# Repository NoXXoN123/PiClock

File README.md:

# PiClock
An Original design of an Analog Digital Clock featuring over 210 LEDs and full customization!

# License
Copyright 2025 NoXXoN

All Rights Reserved.

You may view, download, and manufacture physical copies of this PCB and schematic design for **personal, non-commercial use only** (e.g., DIY projects or prototyping).

You may **not**:
- Distribute, share, or sell the design files or derived works.
- Manufacture boards for sale, resale, or commercial deployment.
- Host or mirror this content online.

For commercial licensing, manufacturing rights, or redistribution permissions, please contact:
noxxonyt@gmail.com

This license applies to all files in this project unless explicitly stated otherwise.

# Schematic
 <br>

# PCB and schematic files
PCB: https://github.com/NoXXoN123/PiClock/blob/main/ClockPi.kicad_pcb  
Schematic: https://github.com/NoXXoN123/PiClock/blob/main/ClockPi.kicad_sch  
Kicad_Pro: https://github.com/NoXXoN123/PiClock/blob/main/ClockPi.kicad_pro  
# How to install
Install Thonny, Install MicroPython on a Pi Pico, Save the code below as 'main.py' on the directory of the Raspberry Pi by opening File Manager in Thonny (View > Files) or use Save As and choose the Raspberry Pi.  
# Code:
main.py:

```
import time
from machine import Pin, PWM, ADC

def percent_to_duty(pct):
    return int((pct / 100.0) * 65535)

def get_light_level():
    raw = light_sensor.read_u16()     # 0–65535
    return raw >> 8                   # Scale to 0–255

def set_pwm_all(level):
    pwm_seconds.duty_u16(level)
    pwm_minutes.duty_u16(level)
    pwm_hours.duty_u16(level)

def light_control_loop():
    while True:
        light = get_light_level()

        if light < LIGHT_THRESHOLD:
            set_pwm_all(DIM_LEVEL)
        else:
            set_pwm_all(BRIGHT_LEVEL)

        time.sleep(0.1)  # Check every 100ms
def shift_out(data_pin, clock_pin, latch_pin, data_bytes):
    latch_pin.value(0)
    for byte in data_bytes:
        for bit in range(8):
            data_pin.value((byte >> (7 - bit)) & 1)
            clock_pin.value(1)
            clock_pin.value(0)
    latch_pin.value(1)
def seconds(*bits):
    # bits is a list of 64 bits for 8 chips * 8 bits
    # convert bits to bytes and send
    data_bytes = []
    for i in range(0, 64, 8):
        byte = 0
        for b in bits[i:i+8]:
            byte = (byte << 1) | (b & 1)
        data_bytes.append(byte)
    shift_out(DATA_PIN_SECONDS, CLOCK_PIN_SECONDS, LATCH_PIN_SECONDS, data_bytes)

def minutes(*bits):
    data_bytes = []
    for i in range(0, 64, 8):
        byte = 0
        for b in bits[i:i+8]:
            byte = (byte << 1) | (b & 1)
        data_bytes.append(byte)
    shift_out(DATA_PIN_MINUTES, CLOCK_PIN_MINUTES, LATCH_PIN_MINUTES, data_bytes)

def hours(*bits):
    data_bytes = []
    for i in range(0, 16, 8):
        byte = 0
        for b in bits[i:i+8]:
            byte = (byte << 1) | (b & 1)
        data_bytes.append(byte)
    shift_out(DATA_PIN_HOURS, CLOCK_PIN_HOURS, LATCH_PIN_HOURS, data_bytes)
def seconds(*bits):
    # your code to shift out bits to the seconds chips
    pass

def minutes(*bits):
    # same for minutes
    pass

def hours(*bits):
    # same for hours
    pass

# Pin setup - Don't touch this!
DATA_PIN_SECONDS = Pin(2, Pin.OUT)
CLOCK_PIN_SECONDS = Pin(3, Pin.OUT)
LATCH_PIN_SECONDS = Pin(4, Pin.OUT)

DATA_PIN_MINUTES = Pin(5, Pin.OUT)
CLOCK_PIN_MINUTES = Pin(6, Pin.OUT)
LATCH_PIN_MINUTES = Pin(7, Pin.OUT)

DATA_PIN_HOURS = Pin(9, Pin.OUT)
CLOCK_PIN_HOURS = Pin(8, Pin.OUT)
LATCH_PIN_HOURS = Pin(10, Pin.OUT)

PHOTORESISTOR_PIN = 26 # ADC0
PWM_SECONDS_PIN = 19
PWM_MINUTES_PIN = 20
PWM_HOURS_PIN = 21
BUTTON_HOUR = Pin(17, Pin.IN, Pin.PULL_DOWN)
BUTTON_MINUTE = Pin(16, Pin.IN, Pin.PULL_DOWN)
LED = Pin(25, Pin.OUT)
# Setup Variables - Don't touch this either!
SECOND_CHIPS = 8
MINUTE_CHIPS = 8
HOUR_CHIPS = 2
# USER SETTINGS - Touch this!
PWM_FREQ = 1000 #Hz DEFAULT: 1000
PWM_BRIGHT = percent_to_duty(60)  # DEFAULT: 60
PWM_DIM = percent_to_duty(10)     # DEFAULT: 10
LIGHT_THRESHOLD = 100 # DEFAULT: 100
# ---------------------
light_sensor = ADC(PHOTORESISTOR_PIN)
pwm_seconds = PWM(Pin(PWM_SECONDS_PIN))
pwm_minutes = PWM(Pin(PWM_MINUTES_PIN))
pwm_hours   = PWM(Pin(PWM_HOURS_PIN))
for pwm in (pwm_seconds, pwm_minutes, pwm_hours):
    pwm.freq(PWM_FREQ)

seconds_buffer = bytearray(SECOND_CHIPS)
minutes_buffer = bytearray(MINUTE_CHIPS)
hours_buffer = bytearray(HOUR_CHIPS)

# ---------------- Functions ----------------
def boot_animation_chase():
    for i in range(64):  # 64 steps for seconds and minutes
        sec_pattern = [0 if j == i else 1 for j in range(64)]
        min_pattern = [0 if j == (i + 20) % 64 else 1 for j in range(64)]  # offset for visual effect
        hr_pattern  = [0 if j == (i % 16) else 1 for j in range(16)]       # wrap 0–15

        seconds(*sec_pattern)
        minutes(*min_pattern)
        hours(*hr_pattern)

        time.sleep(0.03)

def fast_forward_boot(cycle_duration_sec=10):
    total_seconds = 12 * 60 * 60  # 12 hours = 43200 seconds
    delay = cycle_duration_sec / total_seconds

    for seconds_passed in range(total_seconds):
        sec = seconds_passed % 60
        min = (seconds_passed // 60) % 60
        hr  = (seconds_passed // 3600) % 12  # 12-hour format

        sec_buf = [1] * 64
        sec_buf[sec] = 0  # active low
        seconds(*sec_buf)

        min_buf = [1] * 64
        min_buf[min] = 0
        minutes(*min_buf)

        hr_buf = [1] * 16
        hr_buf[hr] = 0
        hours(*hr_buf)

        time.sleep(delay)

def run_clock():
    last_sec_update = 0
    last_min_update = 0
    last_hour_update = 0

    sec = 0
    minute = 0
    hour = 0

    last_button_hour = 0
    last_button_minute = 0
    debounce_ms = 200  # debounce delay

    led_on_time = 0
    led_duration = 200  # ms to keep LED on visibly

    while True:
        now = time.ticks_ms()

        if BUTTON_HOUR.value() == 1 and time.ticks_diff(now, last_button_hour) > debounce_ms:
            hour = (hour + 1) % 12
            hours(*[0 if i == hour else 1 for i in range(16)])
            last_button_hour = now
            last_hour_update = now

        if BUTTON_MINUTE.value() == 1 and time.ticks_diff(now, last_button_minute) > debounce_ms:
            minute = (minute + 1) % 60
            minutes(*[0 if i == minute else 1 for i in range(64)])
            last_button_minute = now
            last_min_update = now

        if time.ticks_diff(now, last_sec_update) >= 1000:
            sec = (sec + 1) % 60
            seconds(*[0 if i == sec else 1 for i in range(64)])
            last_sec_update = now

            LED.value(1)
            led_on_time = now

        if LED.value() == 1 and time.ticks_diff(now, led_on_time) > led_duration:
            LED.value(0)

        if time.ticks_diff(now, last_min_update) >= 60000:
            minute = (minute + 1) % 60
            minutes(*[0 if i == minute else 1 for i in range(64)])
            last_min_update = now

        if time.ticks_diff(now, last_hour_update) >= 3600000:
            hour = (hour + 1) % 12
            hours(*[0 if i == hour else 1 for i in range(16)])
            last_hour_update = now

        light = get_light_level()
        if light < LIGHT_THRESHOLD:
            set_pwm_all(PWM_DIM)
        else:
            set_pwm_all(PWM_BRIGHT)

        time.sleep(0.01) 

boot_animation_chase()
fast_forward_boot(10) # <-- 10 Seconds
run_clock()
```

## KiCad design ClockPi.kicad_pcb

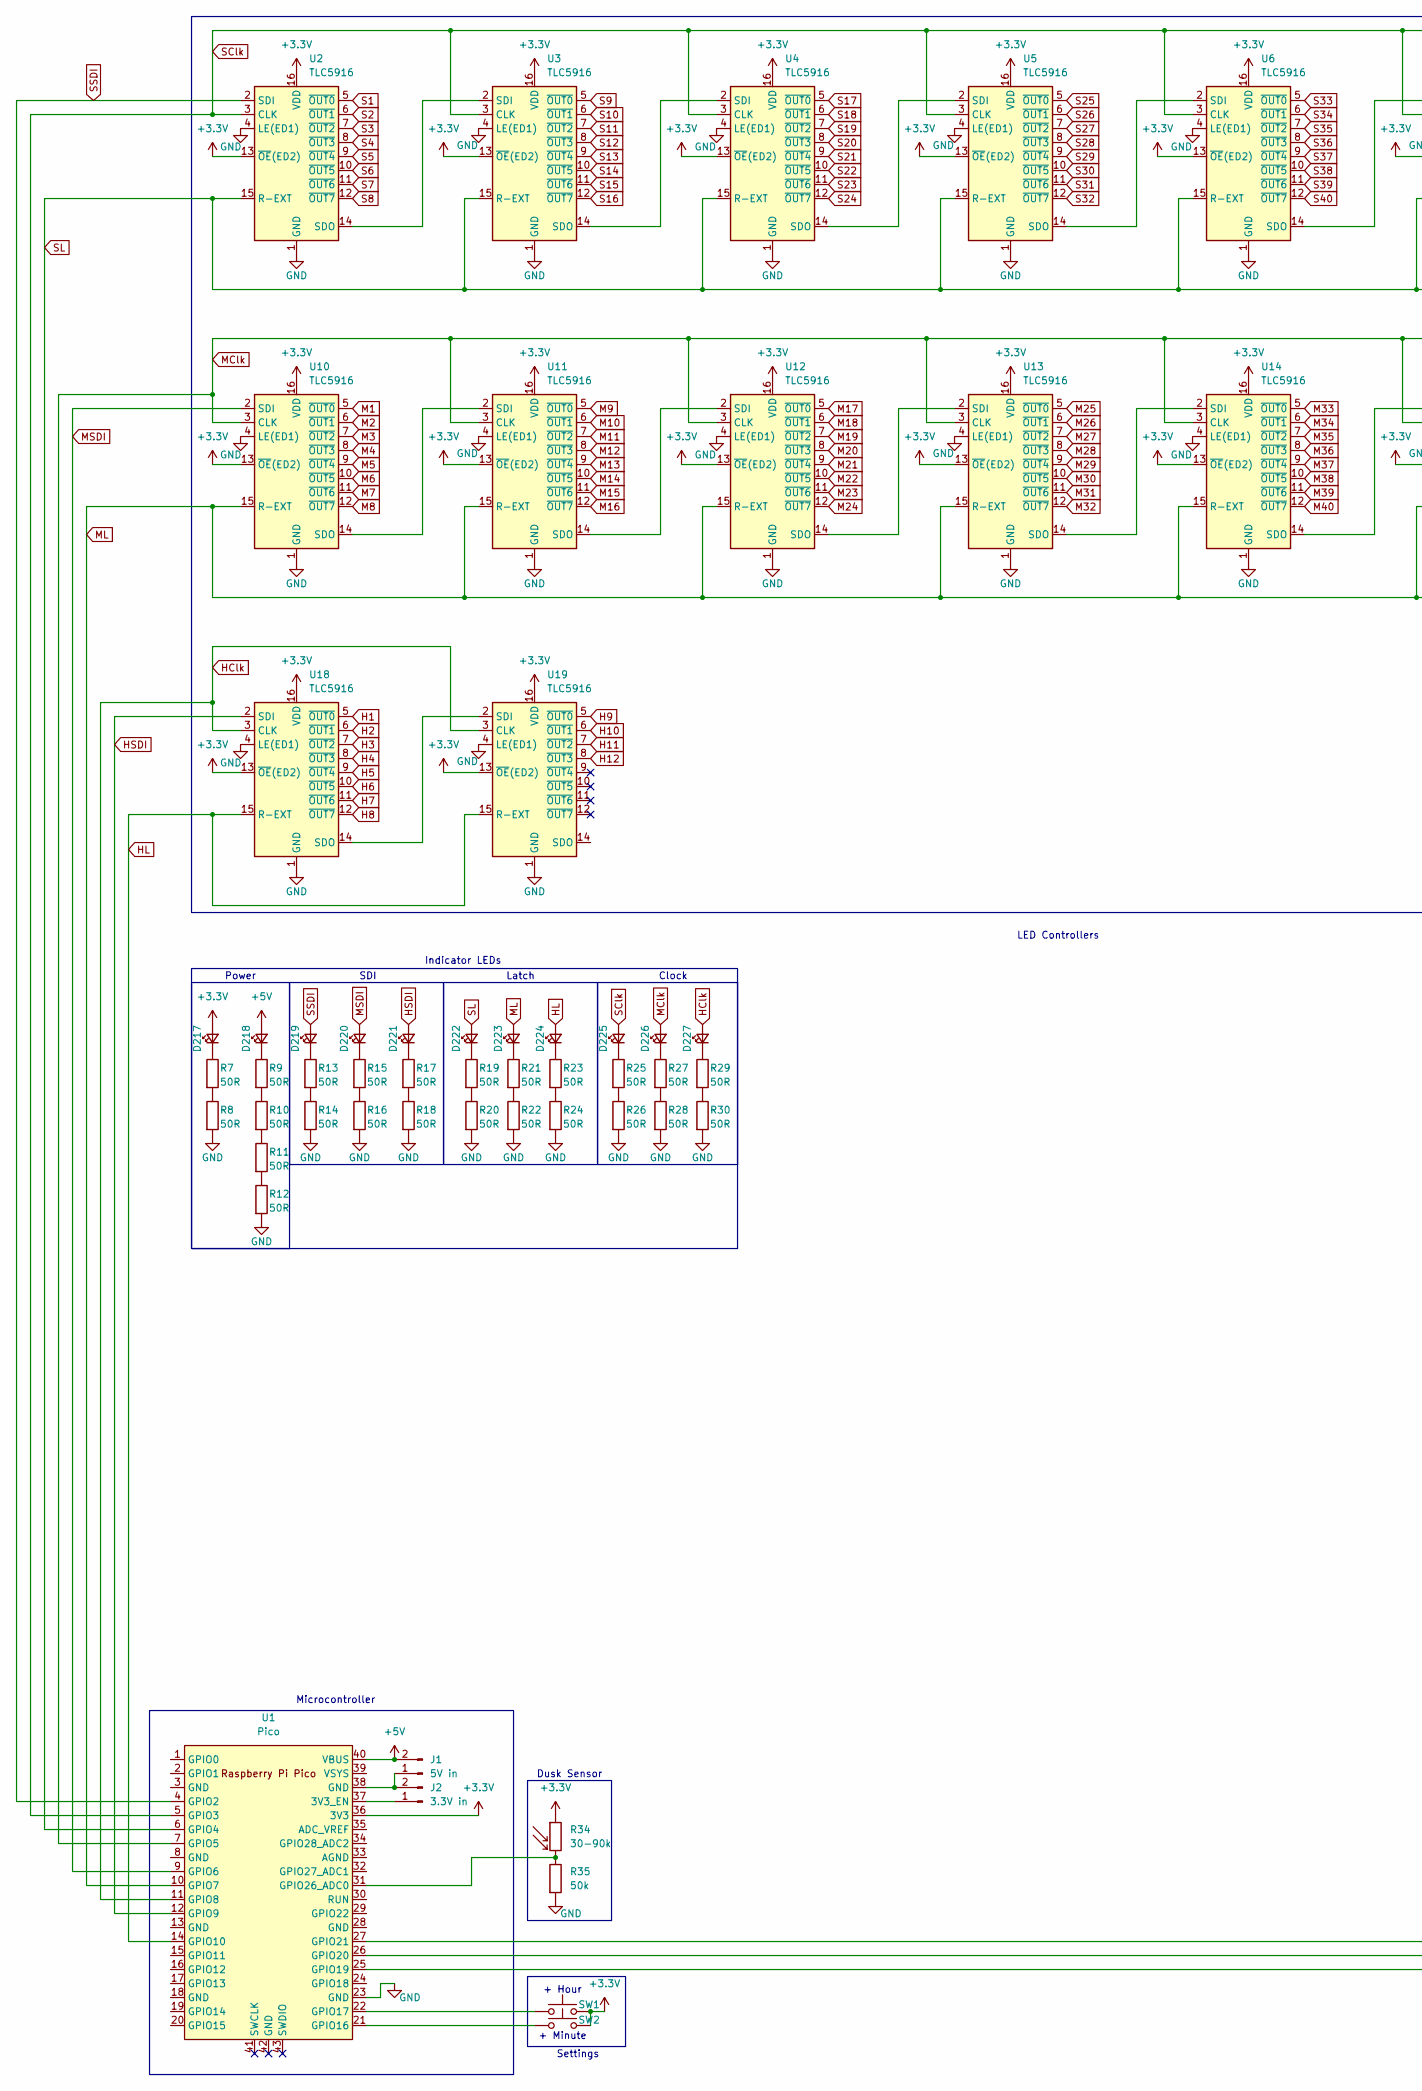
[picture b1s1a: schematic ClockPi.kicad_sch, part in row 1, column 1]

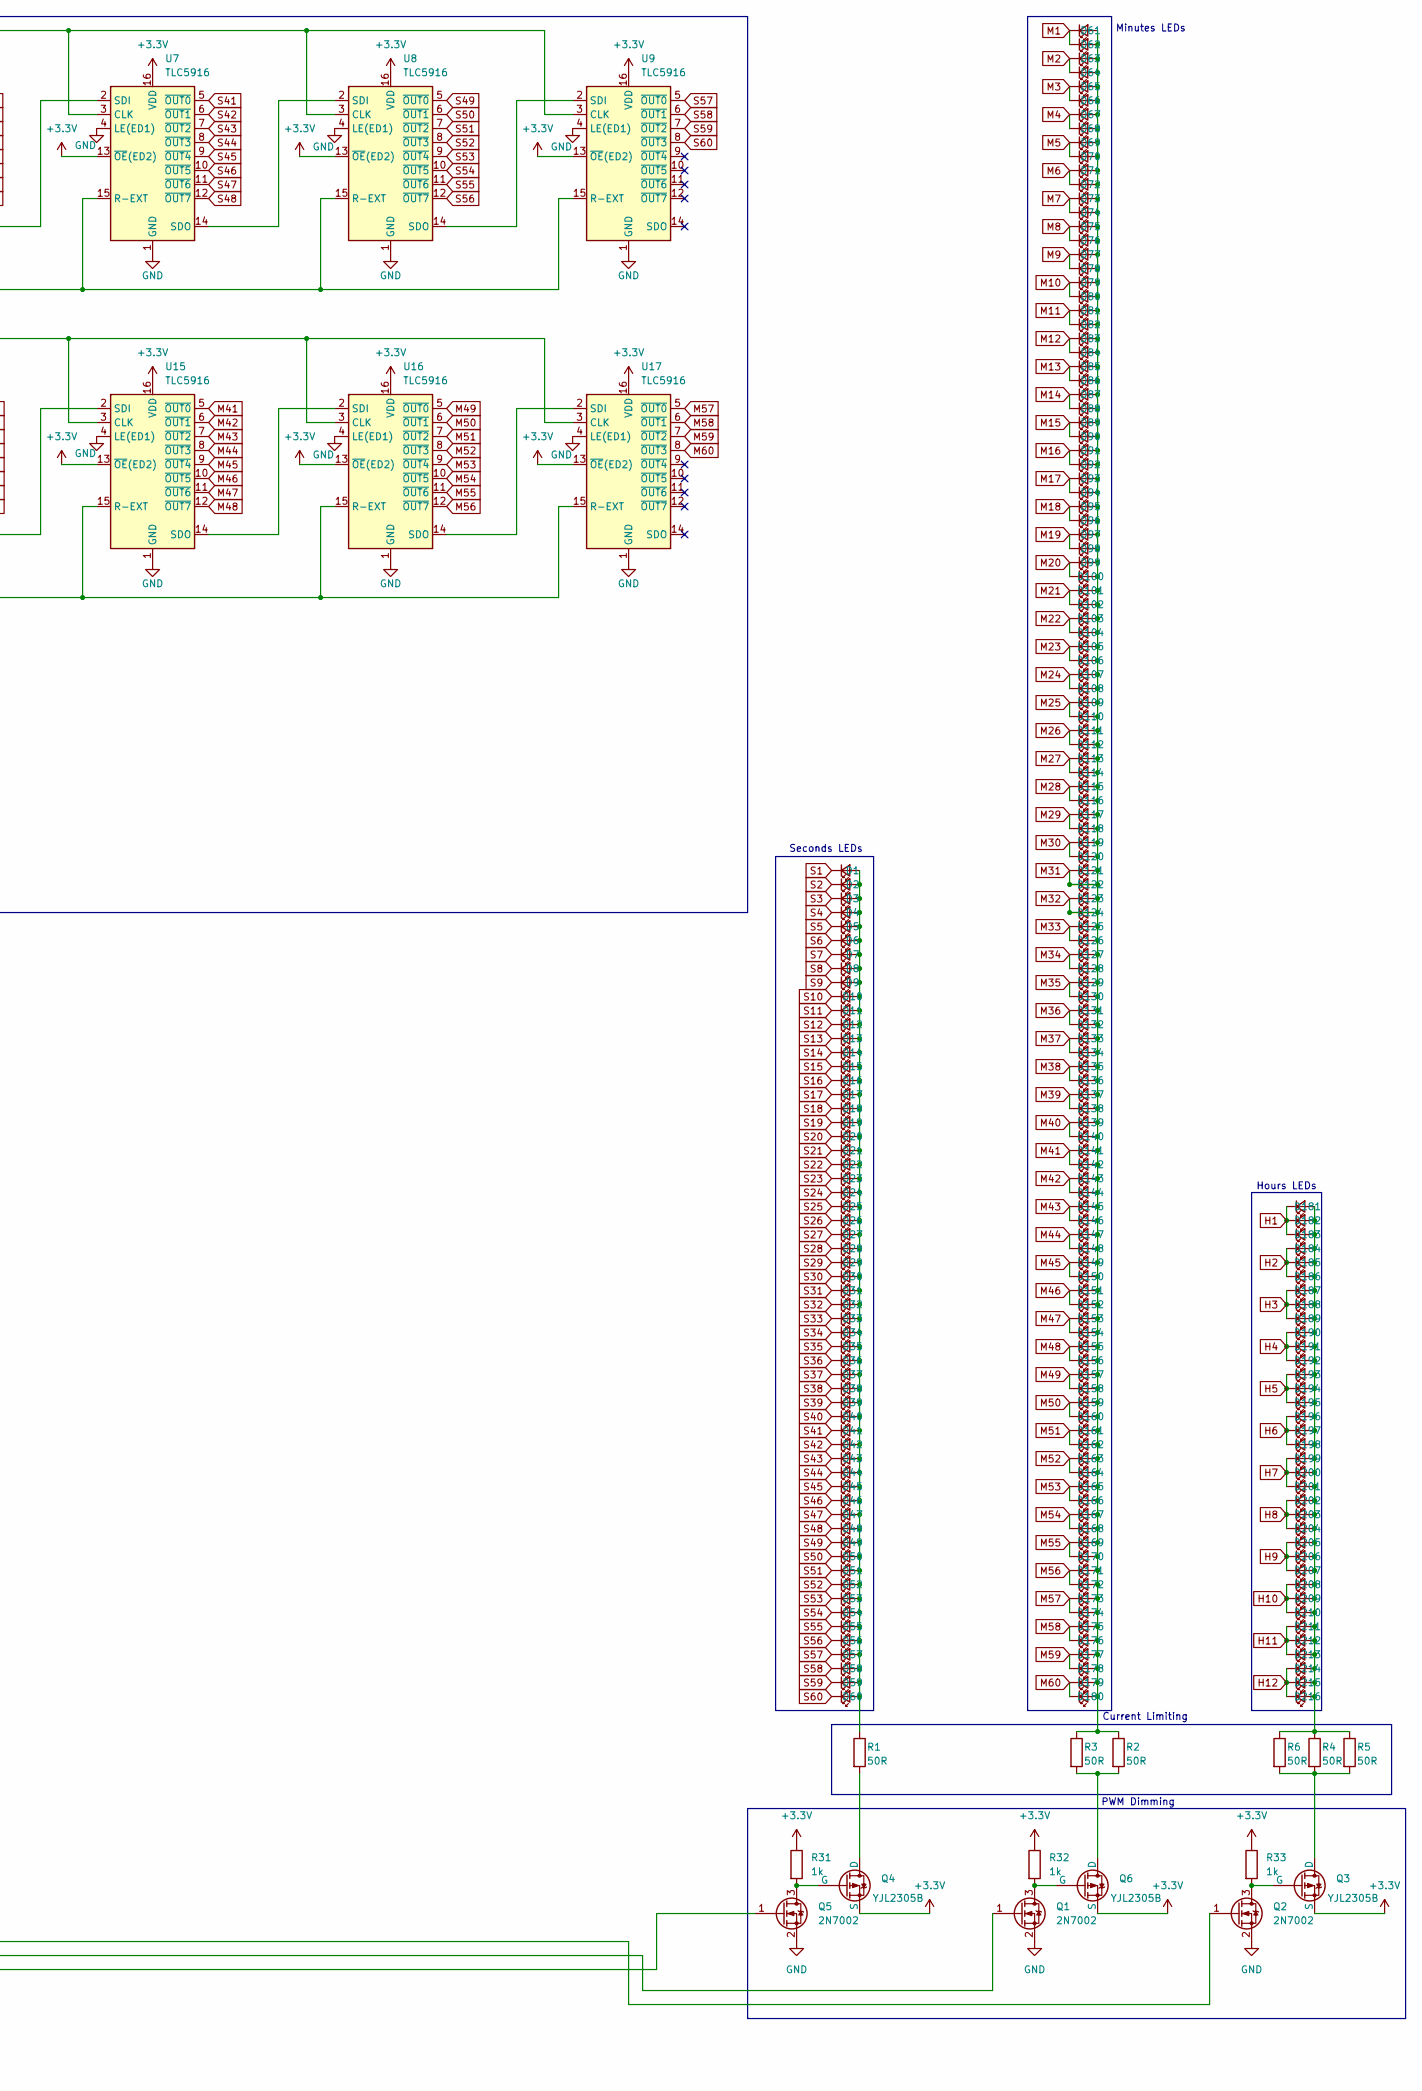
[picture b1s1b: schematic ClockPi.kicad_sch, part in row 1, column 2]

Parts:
D1, D2, D3, D4, D5, D6, D7, D8, D9, D10, D11, D12, D13, D14, D15, D16, D17, D18, D19, D20, D21, D22, D23, D24, D25, D26, D27, D28, D29, D30, D31, D32, D33, D34, D35, D36, D37, D38, D39, D40, D41, D42, D43, D44, D45, D46, D47, D48, D49, D50, D51, D52, D53, D54, D55, D56, D57, D58, D59, D60, D61, D62, D63, D64, D65, D66, D67, D68, D69, D70, D71, D72, D73, D74, D75, D76, D77, D78, D79, D80, D81, D82, D83, D84, D85, D86, D87, D88, D89, D90, D91, D92, D93, D94, D95, D96, D97, D98, D99, D100, D101, D102, D103, D104, D105, D106, D107, D108, D109, D110, D111, D112, D113, D114, D115, D116, D117, D118, D119, D120, D121, D122, D123, D124, D125, D126, D127, D128, D129, D130, D131, D132, D133, D134, D135, D136, D137, D138, D139, D140, D141, D142, D143, D144, D145, D146, D147, D148, D149, D150, D151, D152, D153, D154, D155, D156, D157, D158, D159, D160, D161, D162, D163, D164, D165, D166, D167, D168, D169, D170, D171, D172, D173, D174, D175, D176, D177, D178, D179, D180, D181, D182, D183, D184, D185, D186, D187, D188, D189, D190, D191, D192, D193, D194, D195, D196, D197, D198, D199, D200, D201, D202, D203, D204, D205, D206, D207, D208, D209, D210, D211, D212, D213, D214, D215, D216, D217, D218, D219, D220, D221, D222, D223, D224, D225, D226, D227: LED_Small; LED_0805_2012Metric_Pad1.15x1.40mm_HandSolder
J1: 5V in; PinHeader_1x02_P2.54mm_Vertical
J2: 3.3V in; PinHeader_1x02_P2.54mm_Vertical
Q1, Q2, Q5: 2N7002; SOT-23
Q3, Q4, Q6: YJL2305B; SOT-323_SC-70_Handsoldering
R1, R2, R3, R4, R5, R6, R7, R8, R9, R10, R11, R12, R13, R14, R15, R16, R17, R18, R19, R20, R21, R22, R23, R24, R25, R26, R27, R28, R29, R30: 50R; R_0402_1005Metric_Pad0.72x0.64mm_HandSolder
R31, R32, R33: 1k; R_0402_1005Metric_Pad0.72x0.64mm_HandSolder
R34: 30-90k; R_LDR_5.1x4.3mm_P3.4mm_Vertical
R35: 50k; R_0402_1005Metric_Pad0.72x0.64mm_HandSolder
SW1, SW2: SW_Push; SW_DIP_SPSTx01_Slide_6.7x4.1mm_W6.73mm_P2.54mm_LowProfile_J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
U1: Pico; RaspberryPi_Pico_SMD_HandSolder
U2, U3, U4, U5, U6, U7, U8, U9, U10, U11, U12, U13, U14, U15, U16, U17, U18, U19: TLC5916; SO-16_3.9x9.9mm_P1.27mm

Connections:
+3.3V: D217.2 (A), Q3.3 (S), Q4.3 (S), Q6.3 (S), R31.1, R32.1, R33.1, R34.1, SW1.2, SW2.2, U1.36 (3V3), U2.13 (~OE(ED2)), U2.16 (VDD), U3.13 (~OE(ED2)), U3.16 (VDD), U4.13 (~OE(ED2)), U4.16 (VDD), U5.13 (~OE(ED2)), U5.16 (VDD), U6.13 (~OE(ED2)), U6.16 (VDD), U7.13 (~OE(ED2)), U7.16 (VDD), U8.13 (~OE(ED2)), U8.16 (VDD), U9.13 (~OE(ED2)), U9.16 (VDD), U10.13 (~OE(ED2)), U10.16 (VDD), U11.13 (~OE(ED2)), U11.16 (VDD), U12.13 (~OE(ED2)), U12.16 (VDD), U13.13 (~OE(ED2)), U13.16 (VDD), U14.13 (~OE(ED2)), U14.16 (VDD), U15.13 (~OE(ED2)), U15.16 (VDD), U16.13 (~OE(ED2)), U16.16 (VDD), U17.13 (~OE(ED2)), U17.16 (VDD), U18.13 (~OE(ED2)), U18.16 (VDD), U19.13 (~OE(ED2)), U19.16 (VDD)
+5V: D218.2 (A), J1.2, U1.40 (VBUS)
GND: Q1.2 (S), Q2.2 (S), Q5.2 (S), R8.2, R12.2, R14.2, R16.2, R18.2, R20.2, R22.2, R24.2, R26.2, R28.2, R30.2, R35.2, U1.23 (GND), U2.1 (GND), U2.4 (LE(ED1)), U3.1 (GND), U3.4 (LE(ED1)), U4.1 (GND), U4.4 (LE(ED1)), U5.1 (GND), U5.4 (LE(ED1)), U6.1 (GND), U6.4 (LE(ED1)), U7.1 (GND), U7.4 (LE(ED1)), U8.1 (GND), U8.4 (LE(ED1)), U9.1 (GND), U9.4 (LE(ED1)), U10.1 (GND), U10.4 (LE(ED1)), U11.1 (GND), U11.4 (LE(ED1)), U12.1 (GND), U12.4 (LE(ED1)), U13.1 (GND), U13.4 (LE(ED1)), U14.1 (GND), U14.4 (LE(ED1)), U15.1 (GND), U15.4 (LE(ED1)), U16.1 (GND), U16.4 (LE(ED1)), U17.1 (GND), U17.4 (LE(ED1)), U18.1 (GND), U18.4 (LE(ED1)), U19.1 (GND), U19.4 (LE(ED1))
H1: D181.1 (K), D182.1 (K), D183.1 (K), U18.5 (~OUT0)
H2: D184.1 (K), D185.1 (K), D186.1 (K), U18.6 (~OUT1)
H3: D187.1 (K), D188.1 (K), D189.1 (K), U18.7 (~OUT2)
H4: D190.1 (K), D191.1 (K), D192.1 (K), U18.8 (~OUT3)
H5: D193.1 (K), D194.1 (K), D195.1 (K), U18.9 (~OUT4)
H6: D196.1 (K), D197.1 (K), D198.1 (K), U18.10 (~OUT5)
H7: D199.1 (K), D200.1 (K), D201.1 (K), U18.11 (~OUT6)
H8: D202.1 (K), D203.1 (K), D204.1 (K), U18.12 (~OUT7)
H9: D205.1 (K), D206.1 (K), D207.1 (K), U19.5 (~OUT0)
H10: D208.1 (K), D209.1 (K), D210.1 (K), U19.6 (~OUT1)
H11: D211.1 (K), D212.1 (K), D213.1 (K), U19.7 (~OUT2)
H12: D214.1 (K), D215.1 (K), D216.1 (K), U19.8 (~OUT3)
HClk: D227.2 (A), U1.11 (GPIO8), U18.3 (CLK), U19.3 (CLK)
HL: D224.2 (A), U1.14 (GPIO10), U18.15 (R-EXT), U19.15 (R-EXT)
HSDI: D221.2 (A), U1.12 (GPIO9), U18.2 (SDI)
M1: D61.1 (K), D62.1 (K), U10.5 (~OUT0)
M2: D63.1 (K), D64.1 (K), U10.6 (~OUT1)
M3: D65.1 (K), D66.1 (K), U10.7 (~OUT2)
M4: D67.1 (K), D68.1 (K), U10.8 (~OUT3)
M5: D69.1 (K), D70.1 (K), U10.9 (~OUT4)
M6: D71.1 (K), D72.1 (K), U10.10 (~OUT5)
M7: D73.1 (K), D74.1 (K), U10.11 (~OUT6)
M8: D75.1 (K), D76.1 (K), U10.12 (~OUT7)
M9: D77.1 (K), D78.1 (K), U11.5 (~OUT0)
M10: D79.1 (K), D80.1 (K), U11.6 (~OUT1)
M11: D81.1 (K), D82.1 (K), U11.7 (~OUT2)
M12: D83.1 (K), D84.1 (K), U11.8 (~OUT3)
M13: D85.1 (K), D86.1 (K), U11.9 (~OUT4)
M14: D87.1 (K), D88.1 (K), U11.10 (~OUT5)
M15: D89.1 (K), D90.1 (K), U11.11 (~OUT6)
M16: D91.1 (K), D92.1 (K), U11.12 (~OUT7)
M17: D93.1 (K), D94.1 (K), U12.5 (~OUT0)
M18: D95.1 (K), D96.1 (K), U12.6 (~OUT1)
M19: D97.1 (K), D98.1 (K), U12.7 (~OUT2)
M20: D99.1 (K), D100.1 (K), U12.8 (~OUT3)
M21: D101.1 (K), D102.1 (K), U12.9 (~OUT4)
M22: D103.1 (K), D104.1 (K), U12.10 (~OUT5)
M23: D105.1 (K), D106.1 (K), U12.11 (~OUT6)
M24: D107.1 (K), D108.1 (K), U12.12 (~OUT7)
M25: D109.1 (K), D110.1 (K), U13.5 (~OUT0)
M26: D111.1 (K), D112.1 (K), U13.6 (~OUT1)
M27: D113.1 (K), D114.1 (K), U13.7 (~OUT2)
M28: D115.1 (K), D116.1 (K), U13.8 (~OUT3)
M29: D117.1 (K), D118.1 (K), U13.9 (~OUT4)
M30: D119.1 (K), D120.1 (K), U13.10 (~OUT5)
M31: D61.2 (A), D62.2 (A), D63.2 (A), D64.2 (A), D65.2 (A), D66.2 (A), D67.2 (A), D68.2 (A), D69.2 (A), D70.2 (A), D71.2 (A), D72.2 (A), D73.2 (A), D74.2 (A), D75.2 (A), D76.2 (A), D77.2 (A), D78.2 (A), D79.2 (A), D80.2 (A), D81.2 (A), D82.2 (A), D83.2 (A), D84.2 (A), D85.2 (A), D86.2 (A), D87.2 (A), D88.2 (A), D89.2 (A), D90.2 (A), D91.2 (A), D92.2 (A), D93.2 (A), D94.2 (A), D95.2 (A), D96.2 (A), D97.2 (A), D98.2 (A), D99.2 (A), D100.2 (A), D101.2 (A), D102.2 (A), D103.2 (A), D104.2 (A), D105.2 (A), D106.2 (A), D107.2 (A), D108.2 (A), D109.2 (A), D110.2 (A), D111.2 (A), D112.2 (A), D113.2 (A), D114.2 (A), D115.2 (A), D116.2 (A), D117.2 (A), D118.2 (A), D119.2 (A), D120.2 (A), D121.1 (K), D121.2 (A), D122.1 (K), D122.2 (A), D123.1 (K), D123.2 (A), D124.1 (K), D124.2 (A), D125.2 (A), D126.2 (A), D127.2 (A), D128.2 (A), D129.2 (A), D130.2 (A), D131.2 (A), D132.2 (A), D133.2 (A), D134.2 (A), D135.2 (A), D136.2 (A), D137.2 (A), D138.2 (A), D139.2 (A), D140.2 (A), D141.2 (A), D142.2 (A), D143.2 (A), D144.2 (A), D145.2 (A), D146.2 (A), D147.2 (A), D148.2 (A), D149.2 (A), D150.2 (A), D151.2 (A), D152.2 (A), D153.2 (A), D154.2 (A), D155.2 (A), D156.2 (A), D157.2 (A), D158.2 (A), D159.2 (A), D160.2 (A), D161.2 (A), D162.2 (A), D163.2 (A), D164.2 (A), D165.2 (A), D166.2 (A), D167.2 (A), D168.2 (A), D169.2 (A), D170.2 (A), D171.2 (A), D172.2 (A), D173.2 (A), D174.2 (A), D175.2 (A), D176.2 (A), D177.2 (A), D178.2 (A), D179.2 (A), D180.2 (A), R2.1, R3.1, U13.11 (~OUT6), U13.12 (~OUT7)
M33: D125.1 (K), D126.1 (K), U14.5 (~OUT0)
M34: D127.1 (K), D128.1 (K), U14.6 (~OUT1)
M35: D129.1 (K), D130.1 (K), U14.7 (~OUT2)
M36: D131.1 (K), D132.1 (K), U14.8 (~OUT3)
M37: D133.1 (K), D134.1 (K), U14.9 (~OUT4)
M38: D135.1 (K), D136.1 (K), U14.10 (~OUT5)
M39: D137.1 (K), D138.1 (K), U14.11 (~OUT6)
M40: D139.1 (K), D140.1 (K), U14.12 (~OUT7)
M41: D141.1 (K), D142.1 (K), U15.5 (~OUT0)
M42: D143.1 (K), D144.1 (K), U15.6 (~OUT1)
M43: D145.1 (K), D146.1 (K), U15.7 (~OUT2)
M44: D147.1 (K), D148.1 (K), U15.8 (~OUT3)
M45: D149.1 (K), D150.1 (K), U15.9 (~OUT4)
M46: D151.1 (K), D152.1 (K), U15.10 (~OUT5)
M47: D153.1 (K), D154.1 (K), U15.11 (~OUT6)
M48: D155.1 (K), D156.1 (K), U15.12 (~OUT7)
M49: D157.1 (K), D158.1 (K), U16.5 (~OUT0)
M50: D159.1 (K), D160.1 (K), U16.6 (~OUT1)
M51: D161.1 (K), D162.1 (K), U16.7 (~OUT2)
M52: D163.1 (K), D164.1 (K), U16.8 (~OUT3)
M53: D165.1 (K), D166.1 (K), U16.9 (~OUT4)
M54: D167.1 (K), D168.1 (K), U16.10 (~OUT5)
M55: D169.1 (K), D170.1 (K), U16.11 (~OUT6)
M56: D171.1 (K), D172.1 (K), U16.12 (~OUT7)
M57: D173.1 (K), D174.1 (K), U17.5 (~OUT0)
M58: D175.1 (K), D176.1 (K), U17.6 (~OUT1)
M59: D177.1 (K), D178.1 (K), U17.7 (~OUT2)
M60: D179.1 (K), D180.1 (K), U17.8 (~OUT3)
MClk: D226.2 (A), U1.7 (GPIO5), U10.3 (CLK), U11.3 (CLK), U12.3 (CLK), U13.3 (CLK), U14.3 (CLK), U15.3 (CLK), U16.3 (CLK), U17.3 (CLK)
ML: D223.2 (A), U1.10 (GPIO7), U10.15 (R-EXT), U11.15 (R-EXT), U12.15 (R-EXT), U13.15 (R-EXT), U14.15 (R-EXT), U15.15 (R-EXT), U16.15 (R-EXT), U17.15 (R-EXT)
MSDI: D220.2 (A), U1.9 (GPIO6), U10.2 (SDI)
unnamed: D1.2 (A), D2.2 (A), D3.2 (A), D4.2 (A), D5.2 (A), D6.2 (A), D7.2 (A), D8.2 (A), D9.2 (A), D10.2 (A), D11.2 (A), D12.2 (A), D13.2 (A), D14.2 (A), D15.2 (A), D16.2 (A), D17.2 (A), D18.2 (A), D19.2 (A), D20.2 (A), D21.2 (A), D22.2 (A), D23.2 (A), D24.2 (A), D25.2 (A), D26.2 (A), D27.2 (A), D28.2 (A), D29.2 (A), D30.2 (A), D31.2 (A), D32.2 (A), D33.2 (A), D34.2 (A), D35.2 (A), D36.2 (A), D37.2 (A), D38.2 (A), D39.2 (A), D40.2 (A), D41.2 (A), D42.2 (A), D43.2 (A), D44.2 (A), D45.2 (A), D46.2 (A), D47.2 (A), D48.2 (A), D49.2 (A), D50.2 (A), D51.2 (A), D52.2 (A), D53.2 (A), D54.2 (A), D55.2 (A), D56.2 (A), D57.2 (A), D58.2 (A), D59.2 (A), D60.2 (A), R1.1
unnamed: D181.2 (A), D182.2 (A), D183.2 (A), D184.2 (A), D185.2 (A), D186.2 (A), D187.2 (A), D188.2 (A), D189.2 (A), D190.2 (A), D191.2 (A), D192.2 (A), D193.2 (A), D194.2 (A), D195.2 (A), D196.2 (A), D197.2 (A), D198.2 (A), D199.2 (A), D200.2 (A), D201.2 (A), D202.2 (A), D203.2 (A), D204.2 (A), D205.2 (A), D206.2 (A), D207.2 (A), D208.2 (A), D209.2 (A), D210.2 (A), D211.2 (A), D212.2 (A), D213.2 (A), D214.2 (A), D215.2 (A), D216.2 (A), R4.1, R5.1, R6.1
unnamed: D217.1 (K), R7.1
unnamed: D218.1 (K), R9.1
unnamed: D219.1 (K), R13.1
unnamed: D220.1 (K), R15.1
unnamed: D221.1 (K), R17.1
unnamed: D222.1 (K), R19.1
unnamed: D223.1 (K), R21.1
unnamed: D224.1 (K), R23.1
unnamed: D225.1 (K), R25.1
unnamed: D226.1 (K), R27.1
unnamed: D227.1 (K), R29.1
unnamed: J1.1, J2.2, U1.38 (GND)
unnamed: J2.1, U1.37 (3V3_EN)
unnamed: Q1.3 (D), Q6.2 (G), R32.2
unnamed: Q1.1 (G), U1.26 (GPIO20)
unnamed: Q2.3 (D), Q3.2 (G), R33.2
unnamed: Q2.1 (G), U1.27 (GPIO21)
unnamed: Q3.1 (D), R4.2, R5.2, R6.2
unnamed: Q4.1 (D), R1.2
unnamed: Q4.2 (G), Q5.3 (D), R31.2
unnamed: Q5.1 (G), U1.25 (GPIO19)
unnamed: Q6.1 (D), R2.2, R3.2
unnamed: R7.2, R8.1
unnamed: R9.2, R10.1
unnamed: R10.2, R11.1
unnamed: R11.2, R12.1
unnamed: R13.2, R14.1
unnamed: R15.2, R16.1
unnamed: R17.2, R18.1
unnamed: R19.2, R20.1
unnamed: R21.2, R22.1
unnamed: R23.2, R24.1
unnamed: R25.2, R26.1
unnamed: R27.2, R28.1
unnamed: R29.2, R30.1
unnamed: SW2.1, U1.21 (GPIO16)
unnamed: SW1.1, U1.22 (GPIO17)
unnamed: R34.2, R35.1, U1.31 (GPIO26_ADC0)
unnamed: U2.14 (SDO), U3.2 (SDI)
unnamed: U3.14 (SDO), U4.2 (SDI)
unnamed: U4.14 (SDO), U5.2 (SDI)
unnamed: U5.14 (SDO), U6.2 (SDI)
unnamed: U6.14 (SDO), U7.2 (SDI)
unnamed: U7.14 (SDO), U8.2 (SDI)
unnamed: U8.14 (SDO), U9.2 (SDI)
unnamed: U10.14 (SDO), U11.2 (SDI)
unnamed: U11.14 (SDO), U12.2 (SDI)
unnamed: U12.14 (SDO), U13.2 (SDI)
unnamed: U13.14 (SDO), U14.2 (SDI)
unnamed: U14.14 (SDO), U15.2 (SDI)
unnamed: U15.14 (SDO), U16.2 (SDI)
unnamed: U16.14 (SDO), U17.2 (SDI)
unnamed: U18.14 (SDO), U19.2 (SDI)
S1: D1.1 (K), U2.5 (~OUT0)
S2: D2.1 (K), U2.6 (~OUT1)
S3: D3.1 (K), U2.7 (~OUT2)
S4: D4.1 (K), U2.8 (~OUT3)
S5: D5.1 (K), U2.9 (~OUT4)
S6: D6.1 (K), U2.10 (~OUT5)
S7: D7.1 (K), U2.11 (~OUT6)
S8: D8.1 (K), U2.12 (~OUT7)
S9: D9.1 (K), U3.5 (~OUT0)
S10: D10.1 (K), U3.6 (~OUT1)
S11: D11.1 (K), U3.7 (~OUT2)
S12: D12.1 (K), U3.8 (~OUT3)
S13: D13.1 (K), U3.9 (~OUT4)
S14: D14.1 (K), U3.10 (~OUT5)
S15: D15.1 (K), U3.11 (~OUT6)
S16: D16.1 (K), U3.12 (~OUT7)
S17: D17.1 (K), U4.5 (~OUT0)
S18: D18.1 (K), U4.6 (~OUT1)
S19: D19.1 (K), U4.7 (~OUT2)
S20: D20.1 (K), U4.8 (~OUT3)
S21: D21.1 (K), U4.9 (~OUT4)
S22: D22.1 (K), U4.10 (~OUT5)
S23: D23.1 (K), U4.11 (~OUT6)
S24: D24.1 (K), U4.12 (~OUT7)
S25: D25.1 (K), U5.5 (~OUT0)
S26: D26.1 (K), U5.6 (~OUT1)
S27: D27.1 (K), U5.7 (~OUT2)
S28: D28.1 (K), U5.8 (~OUT3)
S29: D29.1 (K), U5.9 (~OUT4)
S30: D30.1 (K), U5.10 (~OUT5)
S31: D31.1 (K), U5.11 (~OUT6)
S32: D32.1 (K), U5.12 (~OUT7)
S33: D33.1 (K), U6.5 (~OUT0)
S34: D34.1 (K), U6.6 (~OUT1)
S35: D35.1 (K), U6.7 (~OUT2)
S36: D36.1 (K), U6.8 (~OUT3)
S37: D37.1 (K), U6.9 (~OUT4)
S38: D38.1 (K), U6.10 (~OUT5)
S39: D39.1 (K), U6.11 (~OUT6)
S40: D40.1 (K), U6.12 (~OUT7)
S41: D41.1 (K), U7.5 (~OUT0)
S42: D42.1 (K), U7.6 (~OUT1)
S43: D43.1 (K), U7.7 (~OUT2)
S44: D44.1 (K), U7.8 (~OUT3)
S45: D45.1 (K), U7.9 (~OUT4)
S46: D46.1 (K), U7.10 (~OUT5)
S47: D47.1 (K), U7.11 (~OUT6)
S48: D48.1 (K), U7.12 (~OUT7)
S49: D49.1 (K), U8.5 (~OUT0)
S50: D50.1 (K), U8.6 (~OUT1)
S51: D51.1 (K), U8.7 (~OUT2)
S52: D52.1 (K), U8.8 (~OUT3)
S53: D53.1 (K), U8.9 (~OUT4)
S54: D54.1 (K), U8.10 (~OUT5)
S55: D55.1 (K), U8.11 (~OUT6)
S56: D56.1 (K), U8.12 (~OUT7)
S57: D57.1 (K), U9.5 (~OUT0)
S58: D58.1 (K), U9.6 (~OUT1)
S59: D59.1 (K), U9.7 (~OUT2)
S60: D60.1 (K), U9.8 (~OUT3)
SClk: D225.2 (A), U1.5 (GPIO3), U2.3 (CLK), U3.3 (CLK), U4.3 (CLK), U5.3 (CLK), U6.3 (CLK), U7.3 (CLK), U8.3 (CLK), U9.3 (CLK)
SL: D222.2 (A), U1.6 (GPIO4), U2.15 (R-EXT), U3.15 (R-EXT), U4.15 (R-EXT), U5.15 (R-EXT), U6.15 (R-EXT), U7.15 (R-EXT), U8.15 (R-EXT), U9.15 (R-EXT)
SSDI: D219.2 (A), U1.4 (GPIO2), U2.2 (SDI)

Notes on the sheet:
Microcontroller
Indicator LEDs
Settings
LED Controllers
Power
+ Minute
Seconds LEDs
SDI
PWM Dimming
Minutes LEDs
Dusk Sensor
Current Limiting
Hours LEDs
Latch
+ Hour
Clock

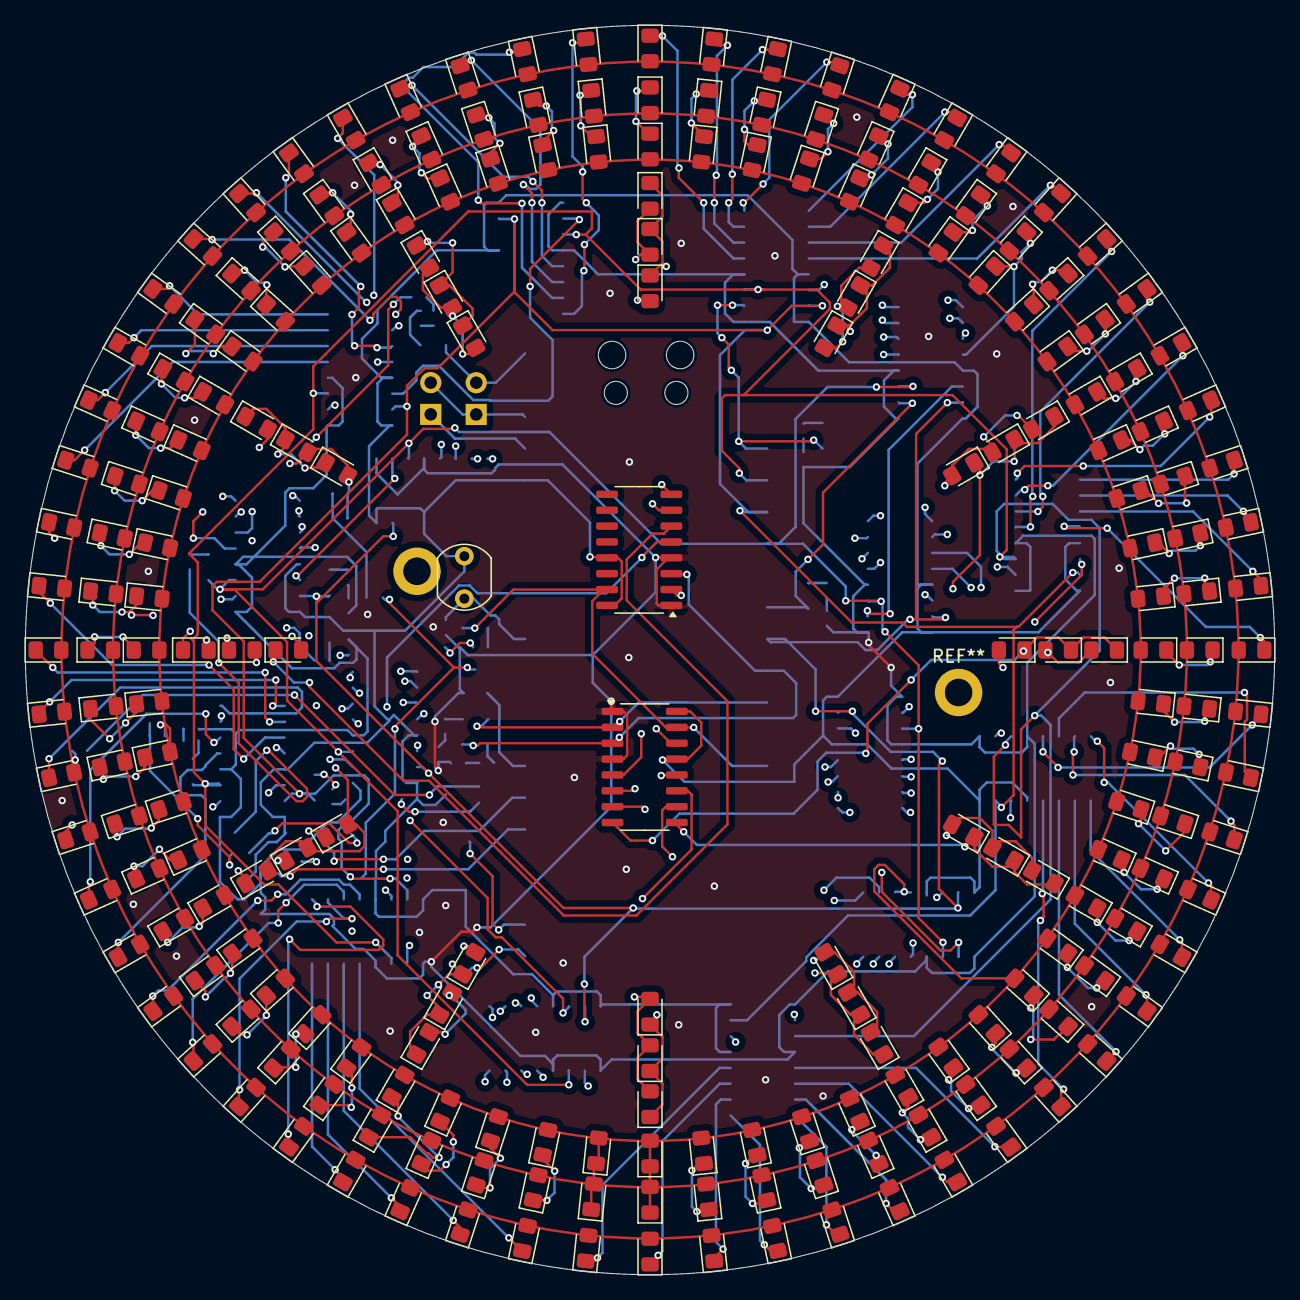
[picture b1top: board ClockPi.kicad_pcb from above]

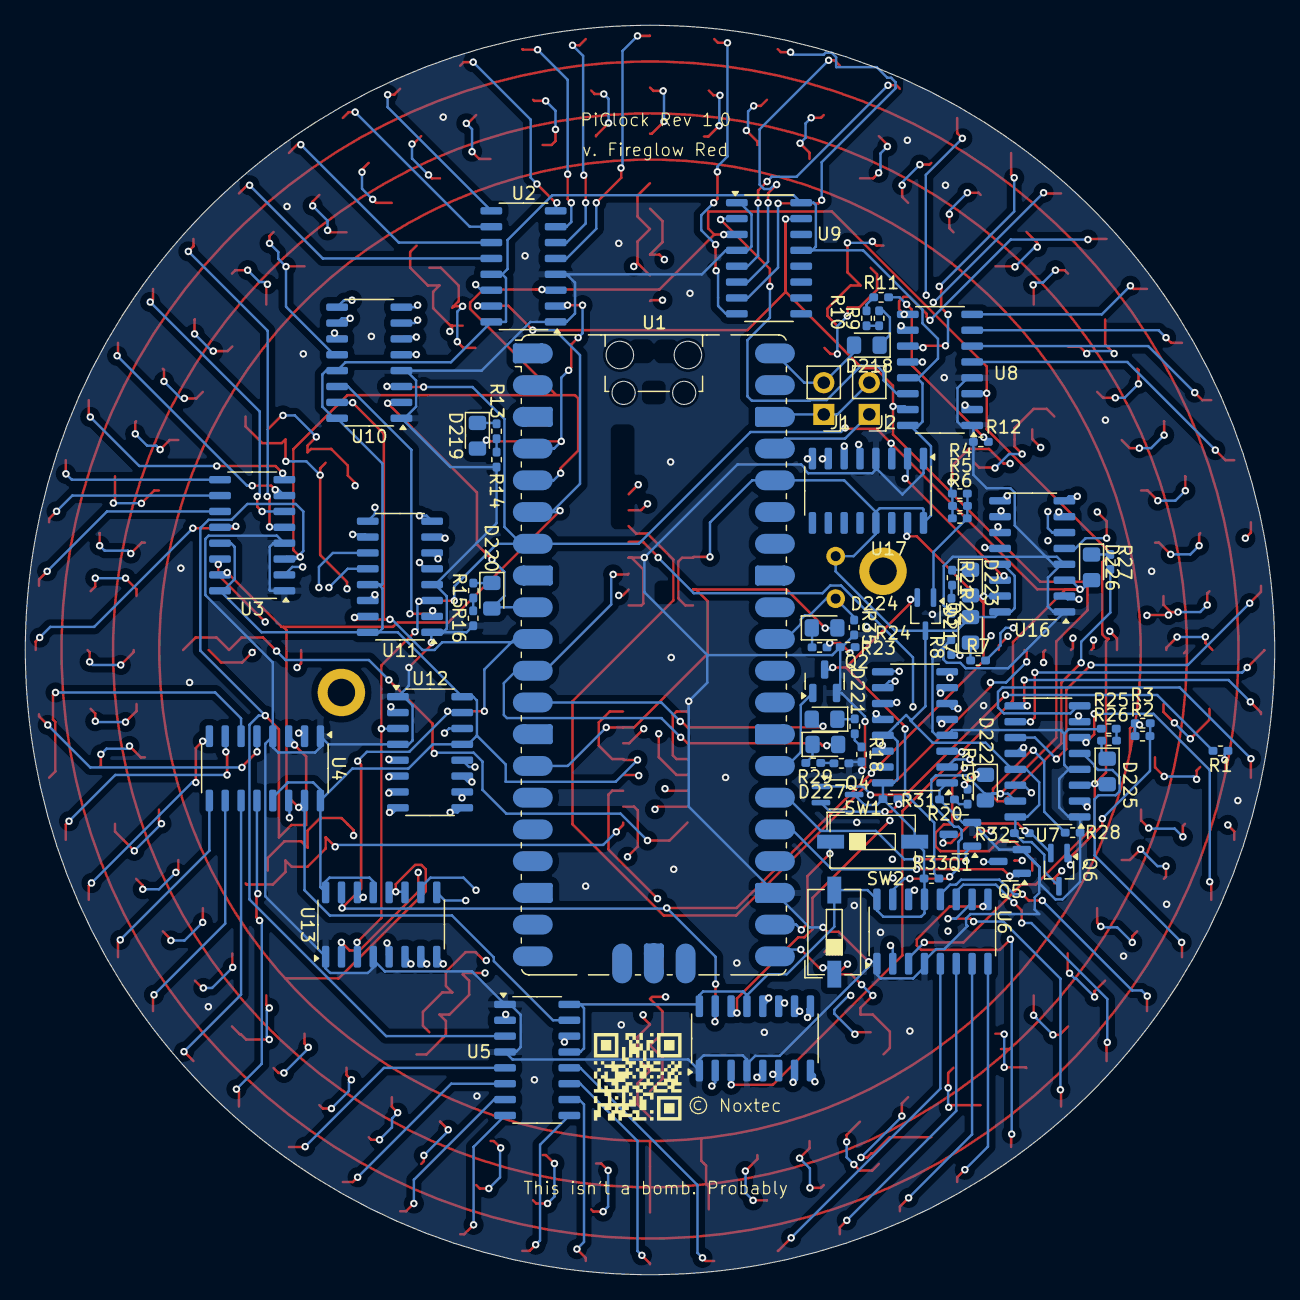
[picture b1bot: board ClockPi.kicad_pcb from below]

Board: 4 copper layers, 100.0 x 100.0 mm, 291 parts (72 on the bottom side), 198 nets.

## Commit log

2025-08-10 Add full schematic PDF

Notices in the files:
ClockPi.kicad_pcb:
© Noxtec
